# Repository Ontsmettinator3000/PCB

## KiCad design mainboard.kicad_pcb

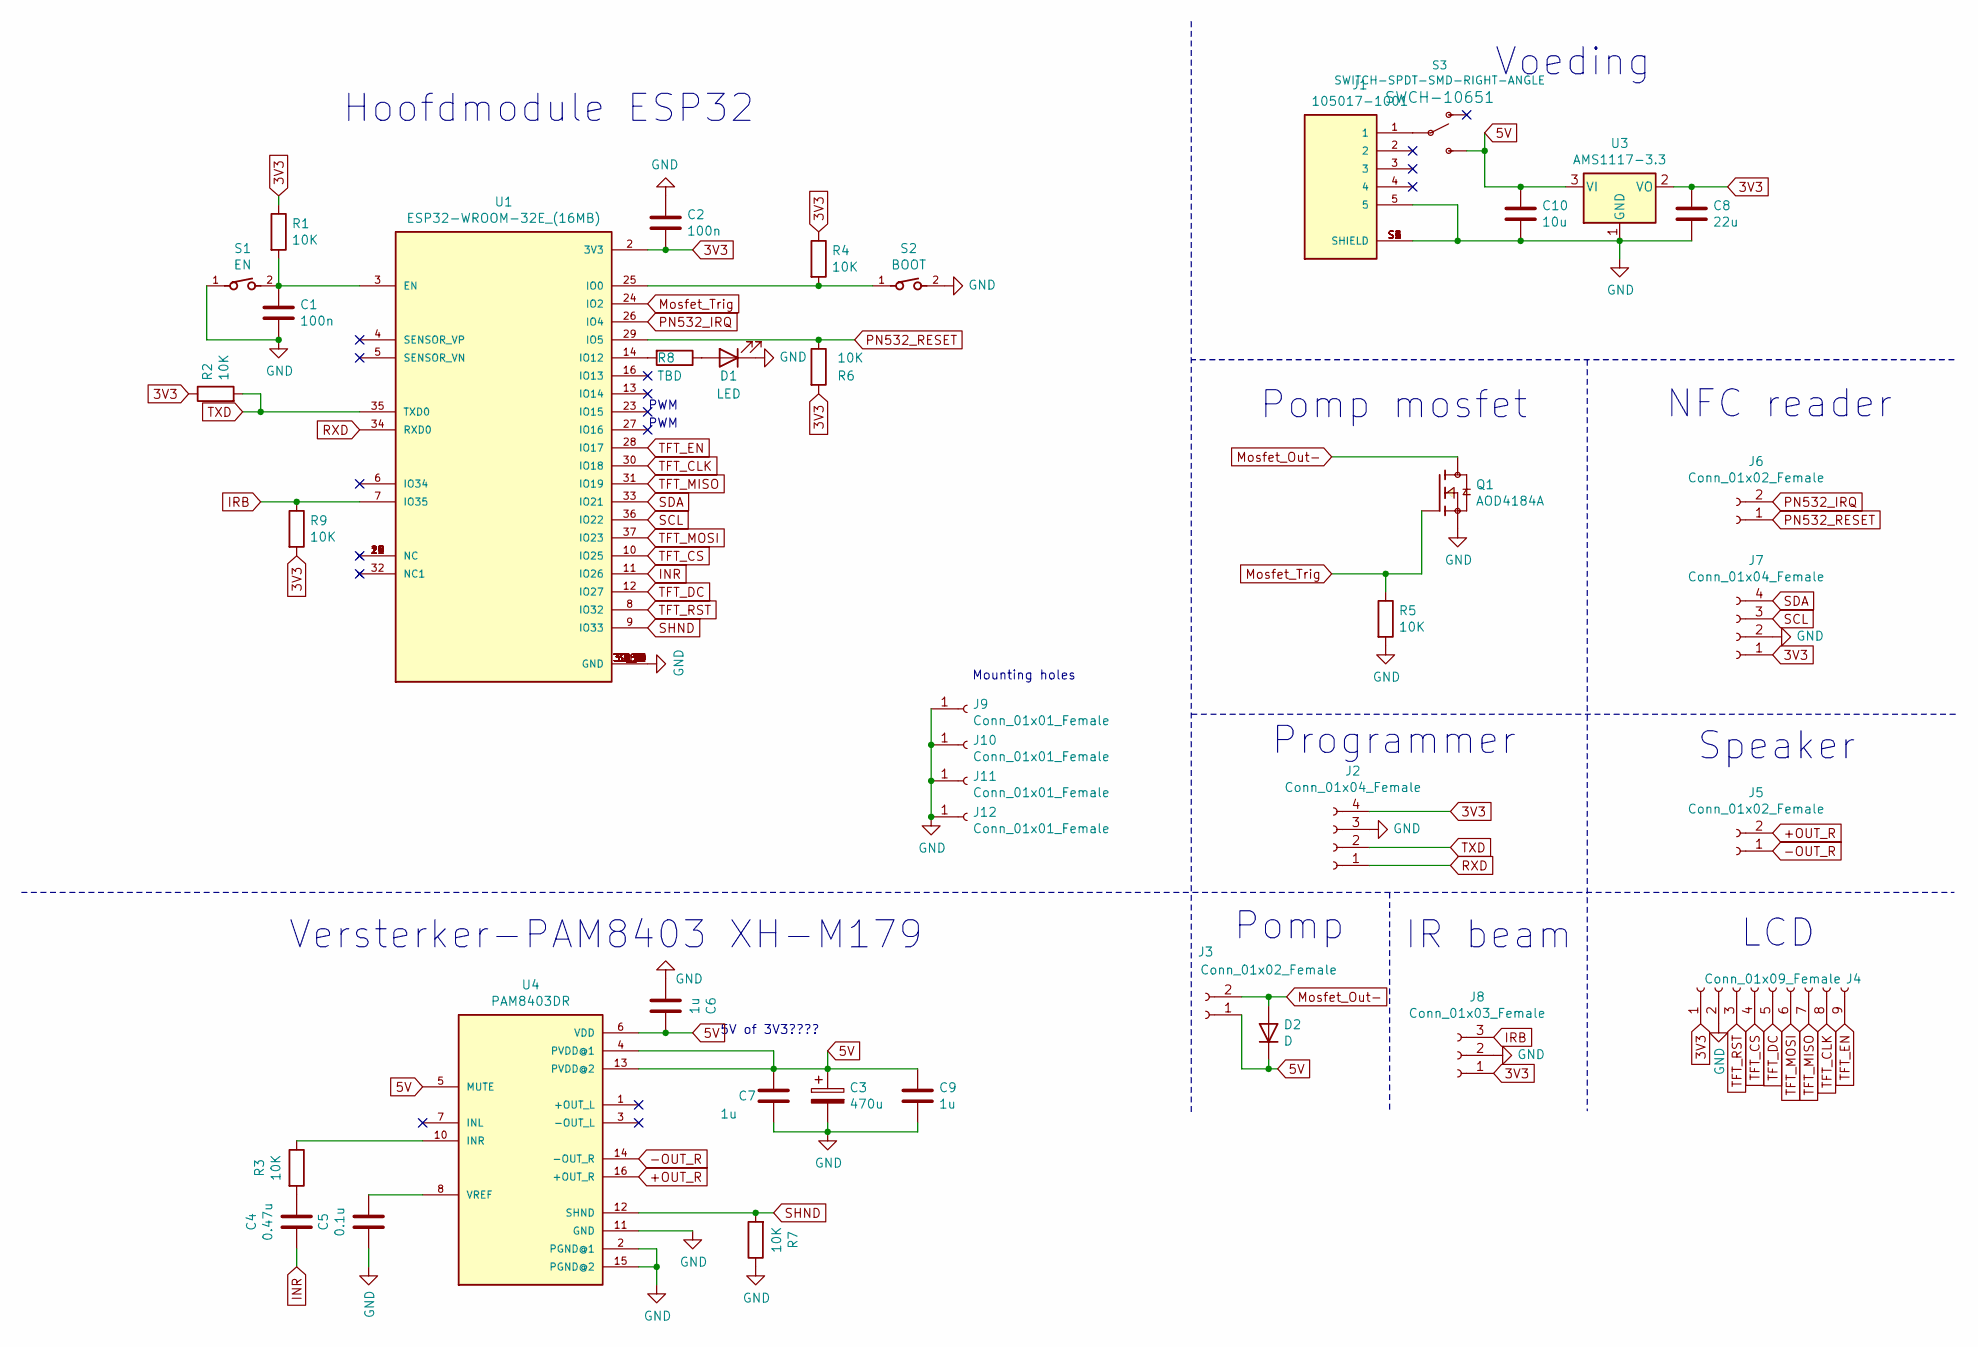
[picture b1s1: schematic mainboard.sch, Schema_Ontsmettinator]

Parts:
C1, C2: 100n; C_0805_2012Metric_Pad1.18x1.45mm_HandSolder
C3: 470u; CP_Radial_D10.0mm_P5.00mm
C4: 0.47u; C_0805_2012Metric_Pad1.18x1.45mm_HandSolder
C5: 0.1u; C_0805_2012Metric_Pad1.18x1.45mm_HandSolder
C6, C7, C9: 1u; C_0805_2012Metric_Pad1.18x1.45mm_HandSolder
C8: 22u; CAPPC3528X210N
C10: 10u; C_0805_2012Metric_Pad1.18x1.45mm_HandSolder
D1: LED; LED_0805_2012Metric_Pad1.15x1.40mm_HandSolder
D2: D; D_0805_2012Metric_Pad1.15x1.40mm_HandSolder
J1: 105017-1001; MOLEX_105017-1001; PARTREV F
J2, J7: Conn_01x04_Female; PinSocket_1x04_P2.54mm_Vertical
J3, J5, J6: Conn_01x02_Female; PinSocket_1x02_P2.54mm_Vertical
J4: Conn_01x09_Female; PinSocket_1x09_P2.54mm_Vertical
J8: Conn_01x03_Female; PinSocket_1x03_P2.54mm_Vertical
J9, J10, J11, J12: Conn_01x01_Female; MountingHole_3.2mm_M3_DIN965
Q1: AOD4184A; DPAK228P994X240-4N; PARTREV 0
R1, R2, R3, R4, R5, R6, R7, R9: 10K; R_0805_2012Metric_Pad1.20x1.40mm_HandSolder
R8: TBD; R_0805_2012Metric_Pad1.20x1.40mm_HandSolder
S1: EN; 434111043826; PART-NUMBER 434111043826
S2: BOOT; 434111043826; PART-NUMBER 434111043826
S3: SWITCH-SPDT-SMD-RIGHT-ANGLE; SWITCH_SPST_SMD_A
U1: ESP32-WROOM-32E_(16MB); MODULE_ESP32-WROOM-32E_(16MB); PARTREV 1.1
U3: AMS1117-3.3; SOT-223-3_TabPin2
U4: PAM8403DR; SOIC127P605X150-16N

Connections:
3V3: C2.2, C8.1, J2.4, J4.1, J7.1, J8.1, R1.1, R2.1, R4.1, R6.2, R9.2, U1.2 (3V3), U3.2 (VO)
5V: C3.1, C6.1, C7.1, C9.1, C10.1, D2.1 (K), J3.1, S3.3 (S), U3.3 (VI), U4.4 (PVDD@1), U4.5 (MUTE), U4.6 (VDD), U4.13 (PVDD@2)
+OUT_R: J5.2, U4.16 (+OUT_R)
-OUT_R: J5.1, U4.14 (-OUT_R)
GND: C1.2, C2.1, C3.2, C5.2, C6.2, C7.2, C8.2, C9.2, C10.2, D1.1 (K), J1.5, J1.S1 (SHIELD), J1.S2 (SHIELD), J1.S3 (SHIELD), J1.S4 (SHIELD), J1.S5 (SHIELD), J1.S6 (SHIELD), J2.3, J4.2, J7.2, J8.2, J9.1, J10.1, J11.1, J12.1, Q1.3, R5.2, R7.1, S1.1, S2.2, S3.2, U1.1 (GND), U1.15 (GND), U1.38 (GND), U1.39_1 (GND), U1.39_2 (GND), U1.39_3 (GND), U1.39_4 (GND), U1.39_5 (GND), U1.39_6 (GND), U1.39_7 (GND), U1.39_8 (GND), U1.39_9 (GND), U1.39_10 (GND), U1.39_11 (GND), U1.39_12 (GND), U1.39_13 (GND), U1.39_14 (GND), U1.39_15 (GND), U1.39_16 (GND), U1.39_17 (GND), U1.39_18 (GND), U1.39_19 (GND), U1.39_20 (GND), U1.39_21 (GND), U3.1 (GND), U4.2 (PGND@1), U4.11 (GND), U4.15 (PGND@2)
INR: C4.2, U1.11 (IO26)
IRB: J8.3, R9.1, U1.7 (IO35)
Mosfet_Out-: D2.2 (A), J3.2, Q1.4
Mosfet_Trig: Q1.1, R5.1, U1.24 (IO2)
unnamed: C1.1, R1.2, S1.2, U1.3 (EN)
unnamed: C4.1, R3.2
unnamed: C5.1, U4.8 (VREF)
unnamed: D1.2 (A), R8.1
unnamed: J1.1, S3.2
unnamed: R3.1, U4.10 (INR)
unnamed: R4.2, S2.1, U1.25 (IO0)
unnamed: R8.2, U1.14 (IO12)
unnamed: U1.17 (NC), U1.18 (NC), U1.19 (NC), U1.20 (NC), U1.21 (NC), U1.22 (NC)
PN532_IRQ: J6.2, U1.26 (IO4)
PN532_RESET: J6.1, R6.1, U1.29 (IO5)
RXD: J2.1, U1.34 (RXD0)
SCL: J7.3, U1.36 (IO22)
SDA: J7.4, U1.33 (IO21)
SHND: R7.2, U1.9 (IO33), U4.12 (SHND)
TFT_CLK: J4.8, U1.30 (IO18)
TFT_CS: J4.4, U1.10 (IO25)
TFT_DC: J4.5, U1.12 (IO27)
TFT_EN: J4.9, U1.28 (IO17)
TFT_MISO: J4.7, U1.31 (IO19)
TFT_MOSI: J4.6, U1.37 (IO23)
TFT_RST: J4.3, U1.8 (IO32)
TXD: J2.2, R2.2, U1.35 (TXD0)

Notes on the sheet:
Pomp mosfet
Voeding
Programmer
Versterker-PAM8403 XH-M179
PWM
Pomp
Speaker
LCD
NFC reader
Hoofdmodule ESP32
IR beam
5V of 3V3????
Mounting holes

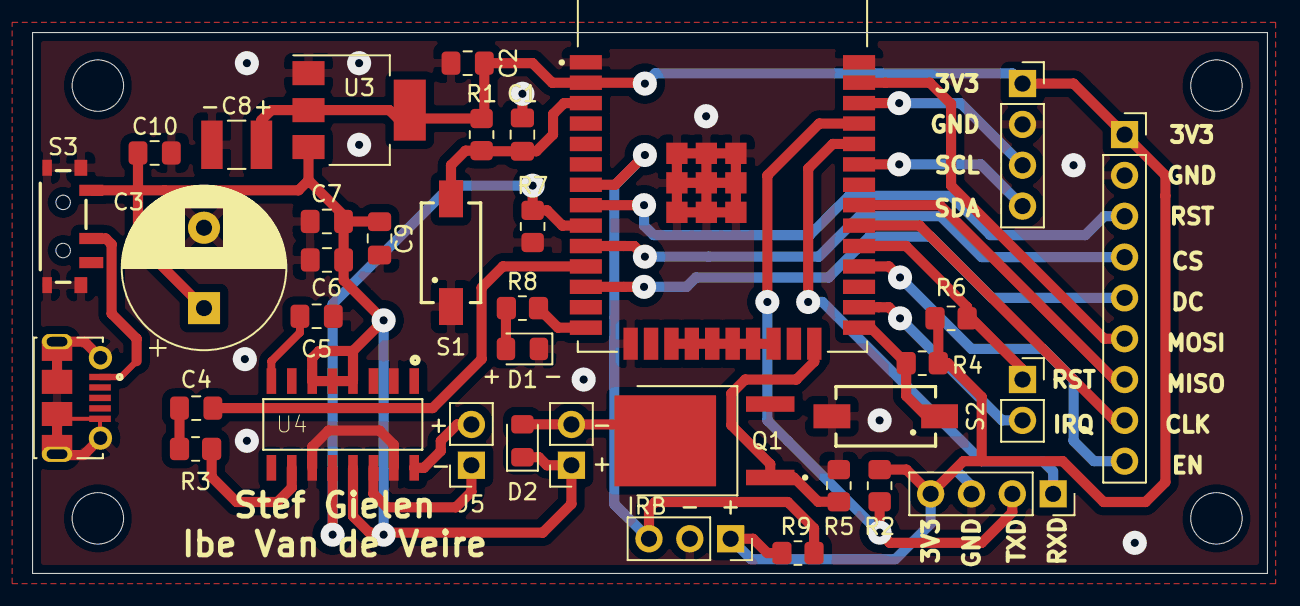
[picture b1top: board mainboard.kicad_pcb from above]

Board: 2 copper layers, 76.8 x 33.7 mm, 36 parts (0 on the bottom side), 32 nets.

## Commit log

2021-03-04 PCB ontwerp
2021-03-05 update
    toevoegen mosfet en versterker in schematic
2021-03-08 ik heb ervoor gezorgd dat de schakeling geen vuurwerk meer is
2021-03-09 condensator toegevoegd aan ldo
2021-03-09 ordenen pcb
    kheb wa plek vrijgelaten voor de io pinnen
2021-03-10 sorry stef
2021-03-11 PCB herwerkt na feedback
2021-03-11 beetje tracing gedaan
2021-03-11 sorry stef pt. 3
2021-03-13 tis fokking mooi wtf
2021-03-13 hij is nu wel echt mooi aan het worden
2021-03-13 een klein detail
2021-03-14 update volgens feedback
    blinkled toegevoegd aan io12
    paar grondvias toegevoegd
    ingangsontkoppeling ldo
2021-03-15 MAND
    elco
2021-03-15 een paar kleine prutsen aangepast, bijna af denk ik
2021-03-15 autisme dankt u
2021-03-15 mounting holes juist gezet
2021-03-15 spam github vol
2021-03-15 Revert "spam github vol"
    This reverts commit 94e953e7b075eab7829dab0ec6791751ecd959af.
2021-03-16 wij waren de ir sensor vergeten, oeps
2021-03-16 tis mis tis mis tis mis tis mis tis miiiiiisssss
2021-03-17 lesupdate
2021-03-17 BIEPBOEP
2021-03-20 checken
    update footprints caps
    dubbele C8 verwijderd
    nfc foute footprint opgelost
    checken van alle esp en versterkerpinnen
2021-03-20 update
    3V3 aan VDD en 5V aan PVDD gehangen van versterker
    (deze commit wegdoen indien niet nodig)
2021-03-20 Revert "update"
    This reverts commit 4af5a32875ec9a07027e92699bf29642d61ca72c.
2021-03-22 condensator vrij gemaakt en hoekjes gefixt
2021-03-22 de pad van de schakelaar waren kapot
2021-04-04 fixes
    -pullup aan IRB
    -mute aan 5V
2021-04-06 fixes
    10k pullup
    mute aan 5V
2021-04-08 diode opgezwierd
2021-04-08 backuppje dabei
2021-04-08 Revert "backuppje dabei"
    This reverts commit f327e6331932bb2f4e665dbf208382180de49052.
2021-04-08 Revert "diode opgezwierd"
    This reverts commit 37b3bf43883e8e94795329db478c9cb5caa1757c.
2021-04-08 amai ik ben er een boeltje van aan het maken
    flyback diode toegevoegd
2021-04-08 gerberberber
    gerberberberberber
2021-04-09 de woordjes staan mooier nu
2021-04-09 mounting holes gefixt
2021-04-10 de zwevende 5v is weg
2021-04-11 finale versie pcb
